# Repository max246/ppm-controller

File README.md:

# PPM Controller
The repo contains schematic to build a simple board with level shift to 3.3V and firmware to control some channels with a FrSky radio (Spektrum has not been tested yet).

## Board
The board has two jacks, one for Frsky( TESTED ) and one for Spektrum ( NOT TESTED ), the idea behind this is to allow a wide range of radio to be connect to the board, Spektrum has the possiblity to read as well but it has not been implemented.

There is a solder jumper to select which LEFT or RIGHT channel to use with Spektrum or potentially other radios otherwise the FrSky jack is fully working and tested.
The level shift IC is a BSS138 with two resistor of 10K ohm.

## Firmware
The firmware can be uploded on any Arduino but it has been tested only on a UNO version, it uses PIN 10 to output the signal and reading from Serial for new values to be set.
The idea is to send a 5 bytes buffer which can be expanded for more channels, but the last slot it just a termial value which is 0X0C.
In the example the system just accepts 0 or 1 as value and it switches between MAX, IDLE and MIN values.

## Issues

If you try to set a PPM value that is out of range, the radio will act as trainer mode is disconnected, make sure you use the correct values for your radio!

## Links

I suggest to watch this video to setup your FrSky/OpenTX radio in trainer mode https://www.youtube.com/watch?v=D9Z40WPyjoQ

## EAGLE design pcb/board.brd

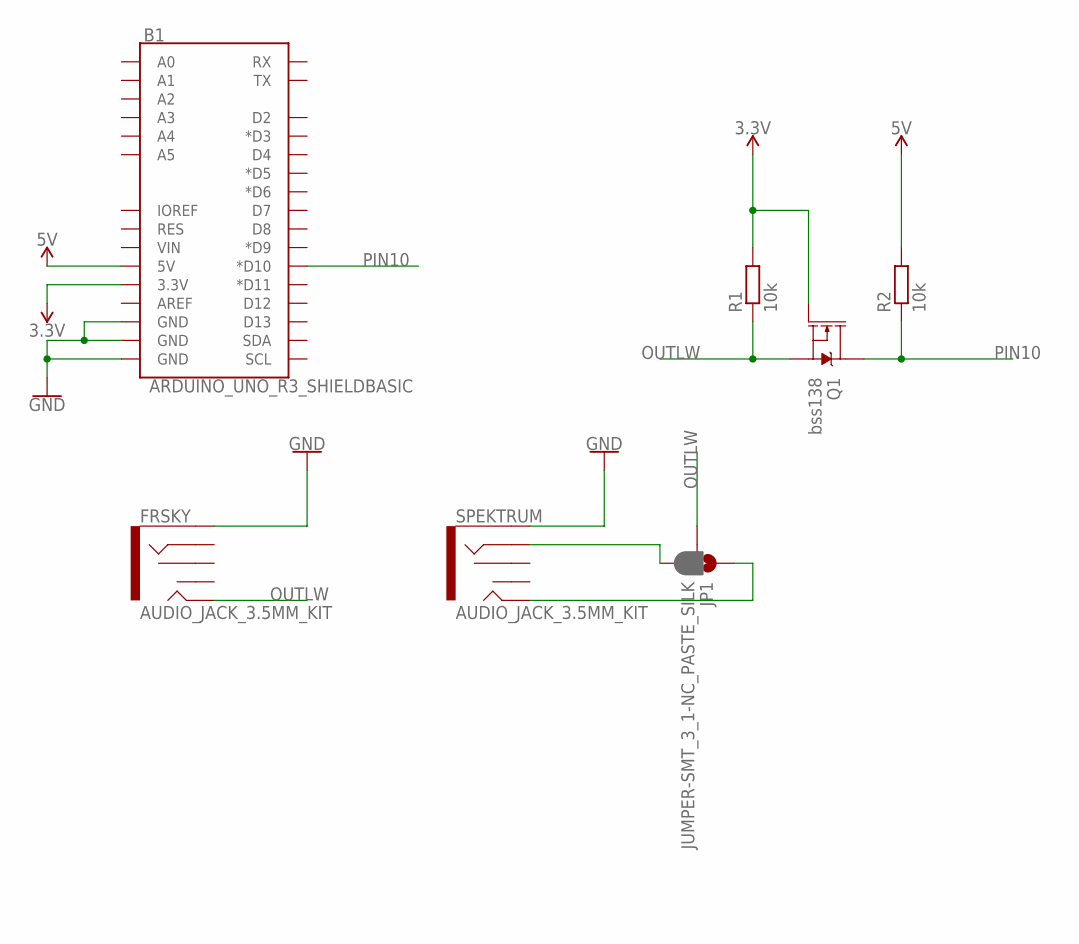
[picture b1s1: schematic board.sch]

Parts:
B1: ARDUINO_UNO_R3_SHIELDBASIC; UNO_R3_SHIELD
FRSKY: AUDIO_JACK_3.5MM_KIT; AUDIO-JACK-KIT
JP1: JUMPER-SMT_3_1-NC_PASTE_SILK; SMT-JUMPER_3_1-NC_PASTE_SILK
Q1: bss138; SOT23-3
R1, R2: 10k; R1206
SPEKTRUM: AUDIO_JACK_3.5MM_KIT; AUDIO-JACK-KIT

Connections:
3.3V: B1.3.3V, Q1.1 (G), R1.2
5V: B1.5V, R2.2
GND: B1.GND@0 (GND), B1.GND@1 (GND), B1.GND@2 (GND), FRSKY.SLEEVE, SPEKTRUM.SLEEVE
unnamed: JP1.1, SPEKTRUM.TIP
unnamed: JP1.3, SPEKTRUM.RING
OUTLW: FRSKY.TIP, JP1.2, Q1.2 (S), R1.1
PIN10: B1.D10 (*D10), Q1.3 (D), R2.1

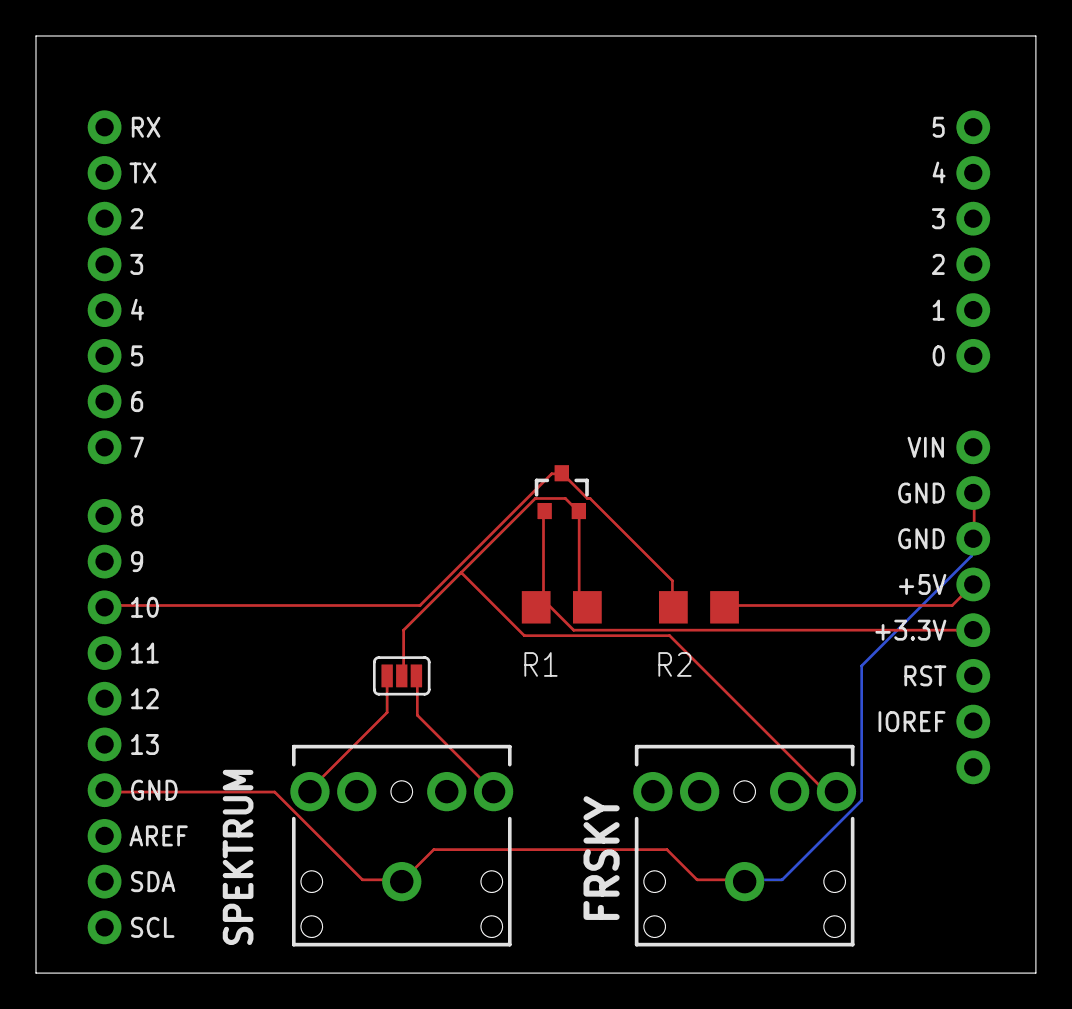
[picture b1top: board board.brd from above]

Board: 2 copper layers, 55.5 x 52.1 mm, 7 parts (0 on the bottom side), 7 nets.

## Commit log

2021-02-17 add project
2021-02-17 add images

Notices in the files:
parts and their libraries:
SparkFun-Boards: Licensing: Creative Commons ShareAlike 4.0 International - https://creativecommons.org/licenses/by-sa/4.0
